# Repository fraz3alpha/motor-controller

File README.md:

# motor-controller
A DC Motor Controller

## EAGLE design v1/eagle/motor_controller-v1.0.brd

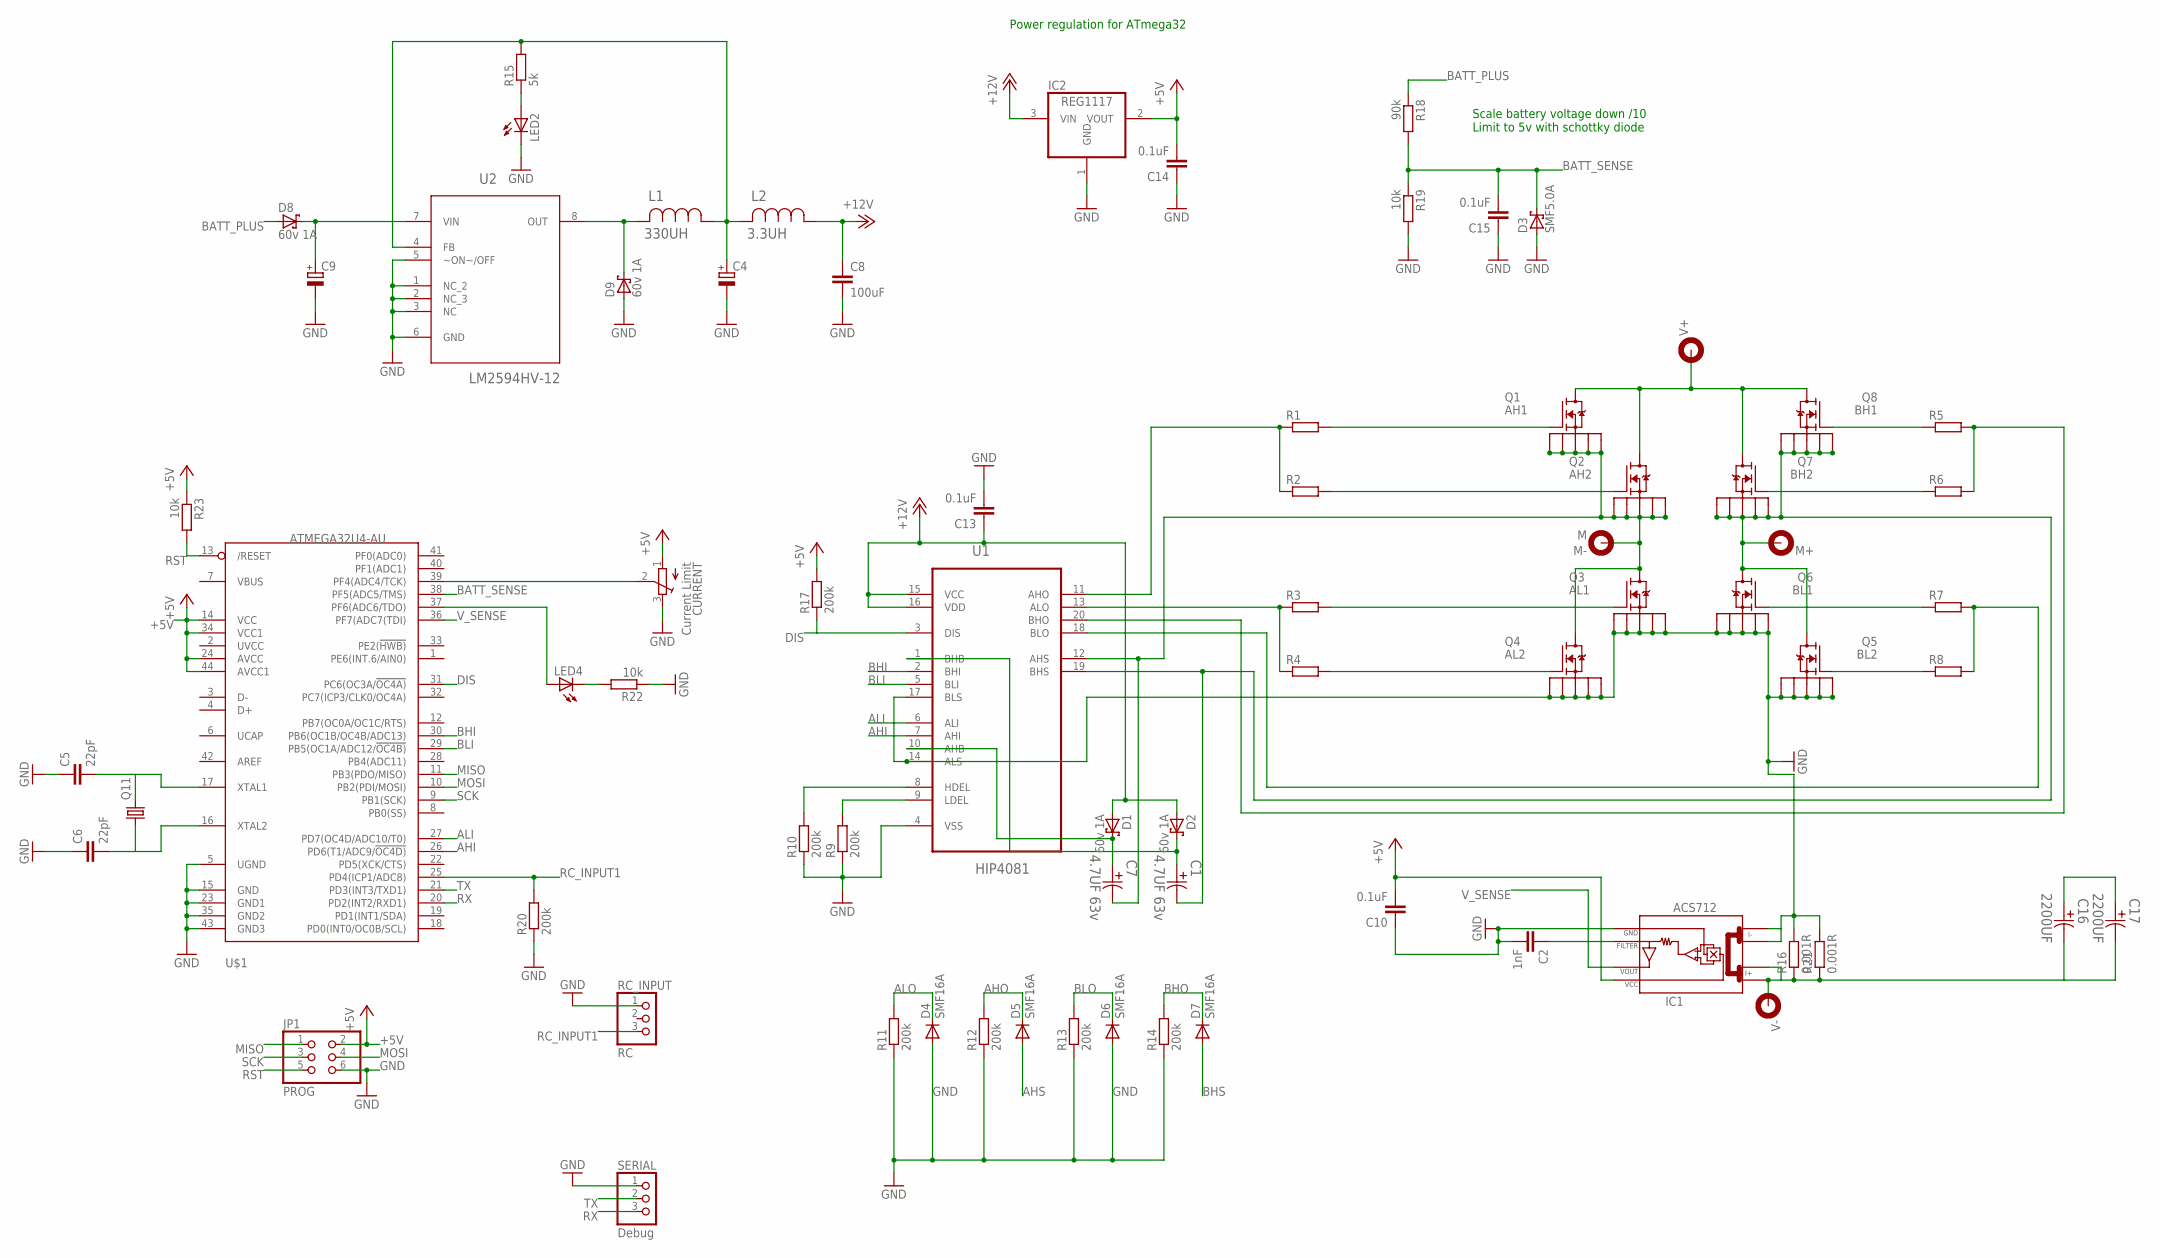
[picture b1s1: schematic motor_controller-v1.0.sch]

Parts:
C1, C7: 4.7UF 63v; CAPAE530X610N
C2: 1nF; C0805
C4: CPOL-EU153CLV-0605; 153CLV-0605
C5, C6: 22pF; C0805K
C8: 100uF; C0805
C9: CPOL-EU153CLV-0810; 153CLV-0810
C10, C13, C14, C15: 0.1uF; C0805
C16, C17: 2200UF; CAPPR750-1800X4000
CURRENT: Current Limit; TC33X
D1, D2, D8, D9: 60v 1A; SOD123FL
D3: SMF5.0A; SOD123FL
D4, D5, D6, D7: SMF16A; SOD-123_MINI-SMA
IC1: ACS712; SO08
IC2: REG1117; SOT223
JP1: PROG; 2X03
L1: 330UH; IND_ELLCTV
L2: 3.3UH; IND_ELL3FU
LED2, LED4: LEDCHIPLED_1206; CHIPLED_1206
M+: MOUNT-PAD-ROUND3.2; 3,2-PAD
M-: M; 3,2-PAD
Q1: AH1; D2PAK-7
Q2: AH2; D2PAK-7
Q3: AL1; D2PAK-7
Q4: AL2; D2PAK-7
Q5: BL2; D2PAK-7
Q6: BL1; D2PAK-7
Q7: BH2; D2PAK-7
Q8: BH1; D2PAK-7
Q11: CRYSTALQC5CB; QC5CB-XTAL
R1, R2, R3, R4, R5, R6, R7, R8: R-EU_M0805; M0805
R9, R10, R11, R12, R13, R14, R17, R20: 200k; M0805
R15: 5k; M0805
R16, R21: 0.001R; R2512
R18: 90k; M0805
R19, R22, R23: 10k; M0805
RC_INPUT: RC; 1X03
SERIAL: Debug; 1X03
U1: HIP4081; SOIC127P1032X265-20N
U2: LM2594HV-12; SOIC127P620X175-8N
U$1: ATMEGA32U4-AU; TQFP44
V+: MOUNT-PAD-ROUND3.2; 3,2-PAD
V-: MOUNT-PAD-ROUND3.2; 3,2-PAD

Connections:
+5V: C10.2, C14.2, CURRENT.1 (A), IC1.8 (VCC), IC2.2 (VOUT), JP1.2, R17.2, R23.1, U$1.14 (VCC), U$1.24 (AVCC), U$1.34 (VCC1), U$1.44 (AVCC1)
+12V: C8.1, C13.1, D1.A, D2.A, IC2.3 (VIN), L2.1, U1.15 (VCC), U1.16 (VDD)
AHI: U1.7 (AHI), U$1.26 (PD6(T1/ADC9/!OC4D))
AHO: D5.C, R1.1, R2.1, R12.2, U1.11 (AHO)
AHS: C7.2, D5.A, M-.B3,2, Q1.S1, Q1.S2, Q1.S3, Q1.S4, Q1.S5, Q2.S1, Q2.S2, Q2.S3, Q2.S4, Q2.S5, Q3.D, Q4.D, U1.12 (AHS)
ALI: U1.6 (ALI), U$1.27 (PD7(OC4D/ADC10/T0))
ALO: D4.C, R3.1, R4.1, R11.2, U1.13 (ALO)
BATT_GND: C16.2, C17.2, IC1.1 (I+_0), IC1.2 (I+_1), R16.1, R21.1, V-.B3,2
BATT_PLUS: C16.1, C17.1, D8.A, Q1.D, Q2.D, Q7.D, Q8.D, R18.1, V+.B3,2
BATT_SENSE: C15.2, D3.C, R18.2, R19.1, U$1.38 (PF5(ADC5/TMS))
BHI: U1.2 (BHI), U$1.30 (PB6(OC1B/OC4B/ADC13))
BHO: D7.C, R5.2, R6.2, R14.2, U1.20 (BHO)
BHS: C1.2, D7.A, M+.B3,2, Q5.D, Q6.D, Q7.S1, Q7.S2, Q7.S3, Q7.S4, Q7.S5, Q8.S1, Q8.S2, Q8.S3, Q8.S4, Q8.S5, U1.19 (BHS)
BLI: U1.5 (BLI), U$1.29 (PB5(OC1A/ADC12/!OC4B))
BLO: D6.C, R7.2, R8.2, R13.2, U1.18 (BLO)
DIS: R17.1, U1.3 (DIS), U$1.31 (PC6(OC3A/!OC4A))
GND: C2.2, C4.-, C5.1, C6.1, C8.2, C9.-, C10.1, C13.2, C14.1, C15.1, CURRENT.3 (E), D3.A, D4.A, D6.A, D9.A, IC1.3 (I-_0), IC1.4 (I-_1), IC1.5 (GND), IC2.1 (GND), JP1.6, LED2.C, Q3.S1, Q3.S2, Q3.S3, Q3.S4, Q3.S5, Q4.S1, Q4.S2, Q4.S3, Q4.S4, Q4.S5, Q5.S1, Q5.S2, Q5.S3, Q5.S4, Q5.S5, Q6.S1, Q6.S2, Q6.S3, Q6.S4, Q6.S5, R9.1, R10.1, R11.1, R12.1, R13.1, R14.1, R16.2, R19.2, R20.1, R21.2, R22.1, RC_INPUT.1, SERIAL.1, U1.4 (VSS), U1.14 (ALS), U1.17 (BLS), U2.1 (NC_2), U2.2 (NC_3), U2.3 (NC), U2.5 (~ON~/OFF), U2.6 (GND), U$1.5 (UGND), U$1.15 (GND), U$1.23 (GND1), U$1.35 (GND2), U$1.43 (GND3)
MISO: JP1.1, U$1.11 (PB3(PDO/MISO))
MOSI: JP1.4, U$1.10 (PB2(PDI/MOSI))
unnamed: C9.+, D8.C, U2.7 (VIN)
unnamed: C4.+, L1.1, L2.2, R15.2, U2.4 (FB)
unnamed: Q1.G, R1.2
unnamed: C2.1, IC1.6 (FILTER)
unnamed: Q2.G, R2.2
unnamed: LED4.A, U$1.37 (PF6(ADC6/TDO))
unnamed: Q3.G, R3.2
unnamed: Q4.G, R4.2
unnamed: LED2.A, R15.1
unnamed: D9.C, L1.2, U2.8 (OUT)
unnamed: Q8.G, R5.1
unnamed: Q7.G, R6.1
unnamed: Q6.G, R7.1
unnamed: Q5.G, R8.1
unnamed: C6.2, Q11.1, U$1.16 (XTAL2)
unnamed: C5.2, Q11.2, U$1.17 (XTAL1)
unnamed: CURRENT.2 (S), U$1.39 (PF4(ADC4/TCK))
unnamed: LED4.C, R22.2
unnamed: R9.2, U1.9 (LDEL)
unnamed: R10.2, U1.8 (HDEL)
unnamed: C7.1, D1.C, U1.10 (AHB)
unnamed: C1.1, D2.C, U1.1 (BHB)
RC_INPUT1: R20.2, RC_INPUT.3, U$1.25 (PD4(ICP1/ADC8))
RST: JP1.5, R23.2, U$1.13 (/RESET)
RX: SERIAL.3, U$1.20 (PD2(INT2/RXD1))
SCK: JP1.3, U$1.9 (PB1(SCK))
TX: SERIAL.2, U$1.21 (PD3(INT3/TXD1))
V_SENSE: IC1.7 (VOUT), U$1.36 (PF7(ADC7(TDI))

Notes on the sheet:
Scale battery voltage down /10 Limit to 5v with schottky diode
Power regulation for ATmega32

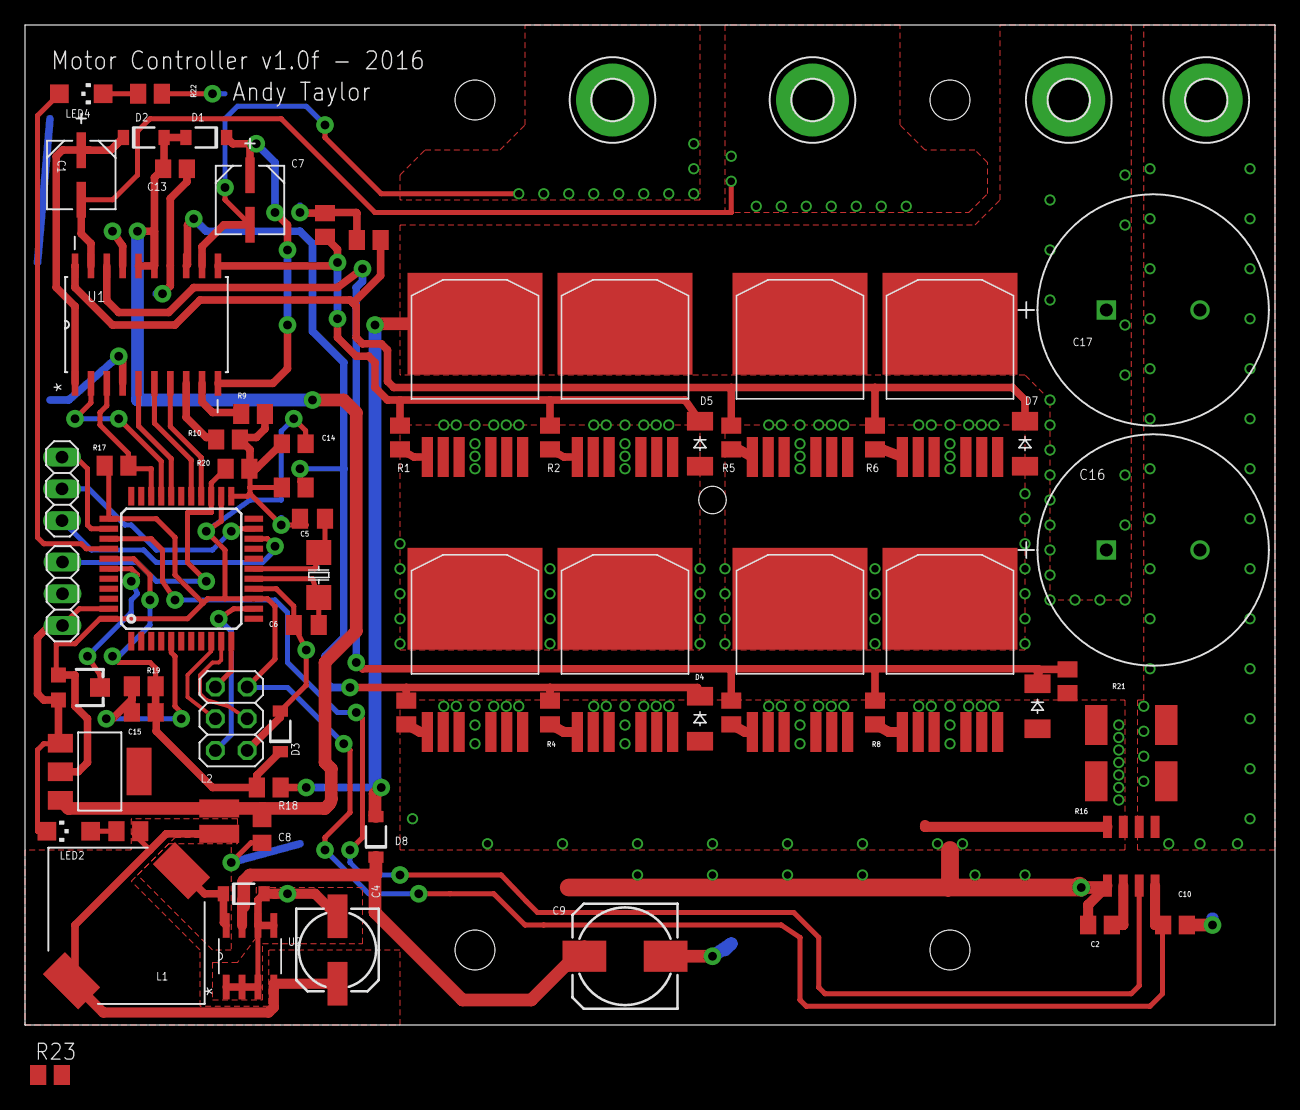
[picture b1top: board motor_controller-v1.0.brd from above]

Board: 2 copper layers, 100.0 x 80.0 mm, 72 parts (0 on the bottom side), 47 nets.

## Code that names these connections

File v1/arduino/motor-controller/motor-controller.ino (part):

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 * 
 * Pins:
 *  OC4A  >  ___  (PC7 - IO 13)
 * #OC4A  >  ___  (PC6 - IO 5)
 * 
 *  OC4B  >  ___  (PB6 - IO 10) BHI
 * #OC4B  >  ___  (PB5 - IO 9)  BLI
 * 
 *  OC4D  >  ___  (PD7 - IO 6)  ALI
 * #OC4D  >  ___  (PD6 - IO 12) AHI
 * 
 * Pay particular note that the HIGH/LOW outputs are inverted between channel A and B
 * for circuit layout reasons. Hopefully this is not a massive headache
 */
#define ALI 6
#define AHI 12

#define BLI 9
#define BHI 10

// Pull the Disable line low to activate the chip
#define DIS 5

// ADCs
#define CURRENT_SENSE_PIN A0
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  * Timer/Counter1 is used to measure the incoming RC pulse
  * 
  * Pins:
  *  ICP1 > PD4 - IO4
  *  
  * Clear timer on rising edge
  * Read capture timer on falling edge
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void setup() {

  // First thing we do is disable the driver chip, so all outputs are low
  pinMode(DIS, OUTPUT);
  digitalWrite(DIS, HIGH);

  // Enable the serial port, configure the debug LED, and flash it to show we are alive
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  pwm_configure();
  
  // Side A
  pinMode(ALI, OUTPUT);
  pinMode(AHI, OUTPUT);
  // Side B
  pinMode(BLI, OUTPUT);
  pinMode(BHI, OUTPUT);


  // Timer1 for RC capture
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
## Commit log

2017-07-26 Initial version of the Arduino code
    - There has been a copy of this floating around on my computer
    for a while, and it is about time that I uploaded it to
    start keeping it in a proper version control system
    - This code needs no external libraries, and I have been
    programming with an 'Arduino as ISP' via the 6 pin
    header
2017-07-26 Add concept README
2017-07-26 Add a bit more to the README
2017-07-31 Add v1.0 Eagle files
    - Also include 1.0f gerbers as sent to dirty pcb
2017-07-31 Add PDF. Might not actually be revision 1.0f, but is close
2017-07-31 Add board layout PDF and rename schematic PDF
